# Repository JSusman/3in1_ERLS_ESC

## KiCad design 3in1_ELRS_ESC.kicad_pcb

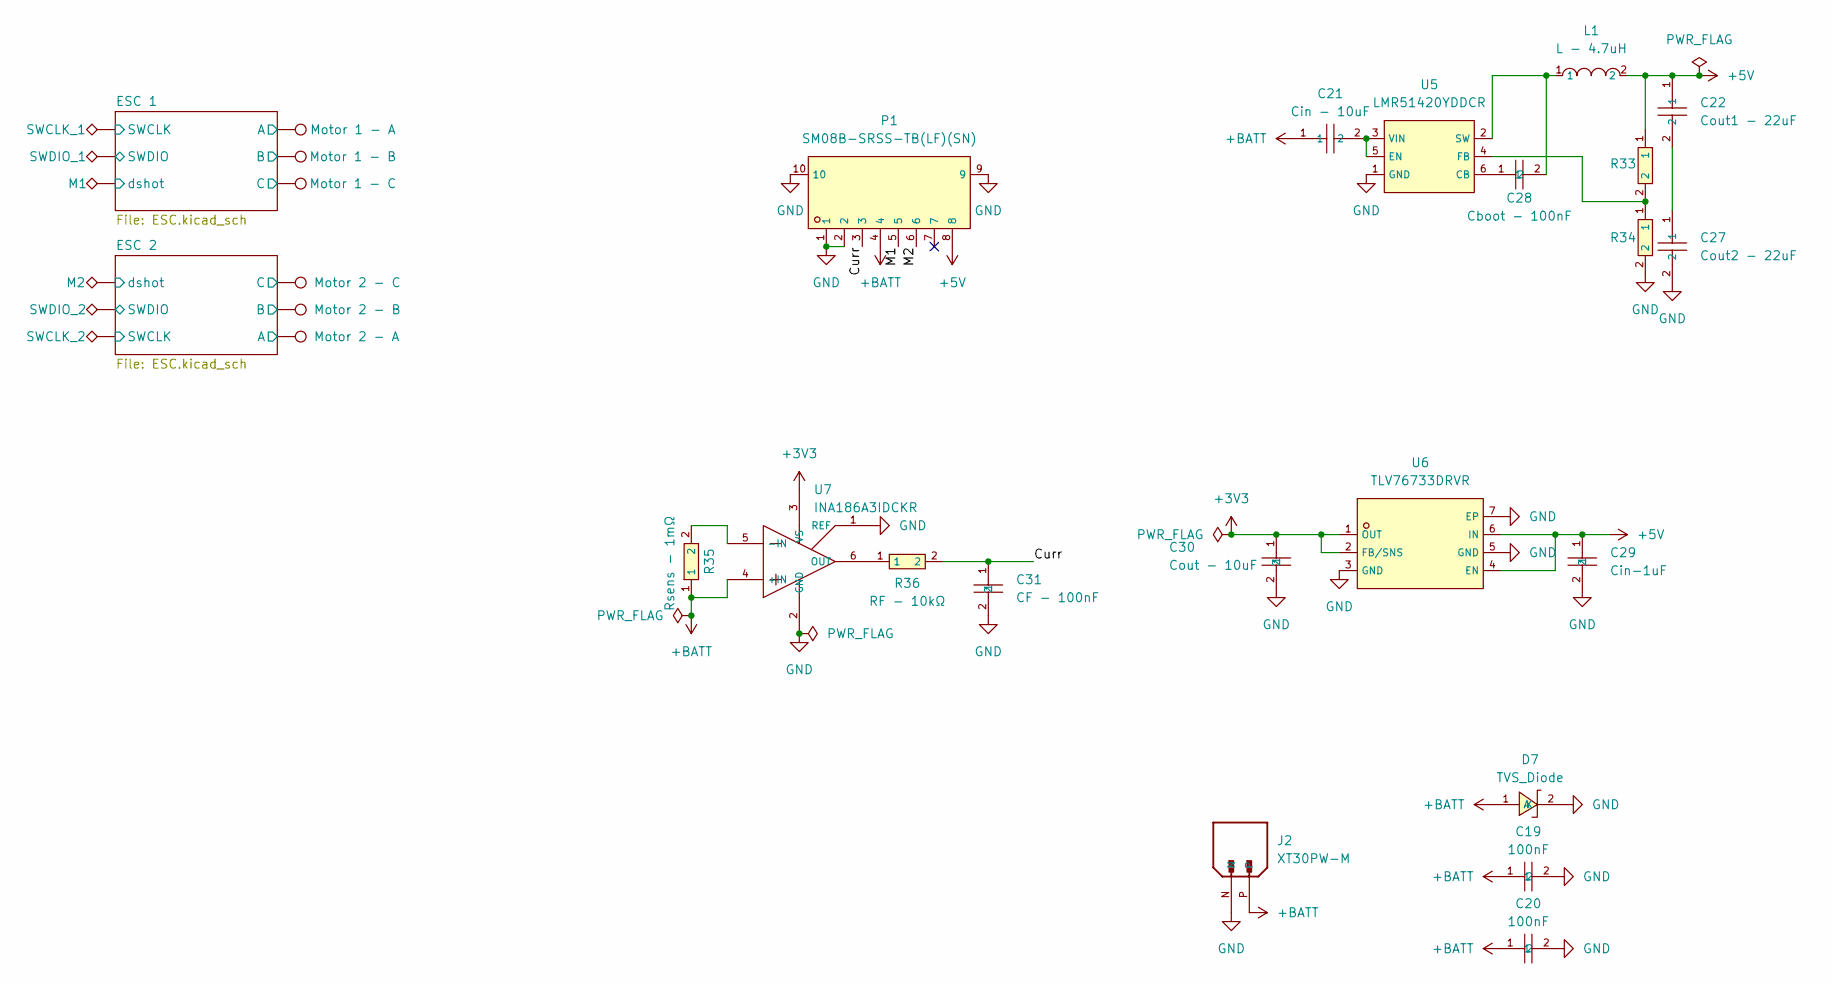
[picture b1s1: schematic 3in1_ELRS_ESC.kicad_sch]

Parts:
A1: Motor 1 - A; TestPoint_THTPad_2.5x2.5mm_Drill1.2mm
A2: Motor 2 - A; TestPoint_THTPad_2.5x2.5mm_Drill1.2mm
B1: Motor 1 - B; TestPoint_THTPad_2.5x2.5mm_Drill1.2mm
B2: Motor 2 - B; TestPoint_THTPad_2.5x2.5mm_Drill1.2mm
C1: Motor 1 - C; TestPoint_THTPad_2.5x2.5mm_Drill1.2mm
C2: Motor 2 - C; TestPoint_THTPad_2.5x2.5mm_Drill1.2mm
C19, C20: 100nF; C76937_C0201; LCSC C76937
C21: Cin - 10uF; C84416_C0805; LCSC C84416
C22: Cout1 - 22uF; C45783_C0805; LCSC C45783
C27: Cout2 - 22uF; C45783_C0805; LCSC C45783
C28: Cboot - 100nF; C76937_C0201; LCSC C76937
C29: Cin-1uF; C14445_C0402; LCSC C14445
C30: Cout - 10uF; C15525_C0402; LCSC C15525
C31: CF - 100nF; C76937_C0201; LCSC C76937
D7: TVS_Diode; C10213_SMB_L4_6-W3_6-LS5_3-RD; LCSC C10213
J2: XT30PW-M; AMASS_XT30PW-M; PARTREV 1.2
L1: L - 4.7uH; C2879693_IND-SMD_L4_5-W4_0; LCSC C2879693
M1, M2: TestPoint_THTPad_2.5x2.5mm_Drill1.2mm
P1: SM08B-SRSS-TB(LF)(SN); C160407_CONN-TH_SM08B-SRSS-TB-LF-SN; LCSC C160407
R33: Rtop - 100KΩ; C25530_R0402; LCSC C25530
R34: Rbot - 16.9KΩ; C11633_R0402; LCSC C11633
R35: Rsens - 1mΩ; C76287_R1206; LCSC C76287
R36: RF - 10kΩ; C149898_R0402; LCSC C149898
SWCLK_1, SWCLK_2: TestPoint_THTPad_2.5x2.5mm_Drill1.2mm
SWDIO_1, SWDIO_2: TestPoint_THTPad_2.5x2.5mm_Drill1.2mm
U5: LMR51420YDDCR; C5383002_SOT-23-6_L2_9-W1_6-P0_95-LS2_9-BL; LCSC C5383002
U6: TLV76733DRVR; C2848334_WSON-6_L2_0-W2_0-P0_65-TL-EP; LCSC C2848334
U7: INA186A3IDCKR; C2058245_SC-70-6_L2_0-W1_3-P0_65-LS2_1-BL-1; LCSC C2058245

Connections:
+3V3: C30.1, U6.1 (OUT), U6.2 (FB/SNS), U7.3 (VS); also elsewhere on the board
+5V: C22.1, C29.1, L1.2, P1.8, R33.1, U6.4 (EN), U6.6 (IN)
+BATT: C19.1, C20.1, C21.1, D7.1 (A), J2.P, P1.4, R35.1, U7.4 (+IN); also elsewhere on the board
/Curr: C31.1, P1.3, R36.2
/ESC 1/Motor A: A1.1 (1_1); also elsewhere on the board
/ESC 1/Motor B: B1.1 (1_1); also elsewhere on the board
/ESC 1/Motor C: C1.1 (1_1); also elsewhere on the board
/ESC 1/SWCLK: SWCLK_1.1 (1_1); also elsewhere on the board
/ESC 1/SWDIO: SWDIO_1.1 (1_1); also elsewhere on the board
/ESC 2/Motor A: A2.1 (1_1); also elsewhere on the board
/ESC 2/Motor B: B2.1 (1_1); also elsewhere on the board
/ESC 2/Motor C: C2.1 (1_1); also elsewhere on the board
/ESC 2/SWCLK: SWCLK_2.1 (1_1); also elsewhere on the board
/ESC 2/SWDIO: SWDIO_2.1 (1_1); also elsewhere on the board
/M1: P1.5
/M2: P1.6
GND: C19.2 (2_2), C20.2 (2_2), C27.2, C29.2, C30.2, C31.2, D7.2 (K), J2.N, P1.1, P1.2, P1.9, P1.10, R34.2, U5.1 (GND), U6.3 (GND), U6.5 (GND), U6.7 (EP), U7.1 (REF), U7.2 (GND); also elsewhere on the board
unnamed: C22.2, C27.1
unnamed: C28.1, U5.6 (CB)
unnamed: C21.2, U5.3 (VIN), U5.5 (EN)
unnamed: R33.2, R34.1, U5.4 (FB)
unnamed: C28.2, L1.1, U5.2 (SW)
unnamed: R35.2, U7.5 (-IN)
unnamed: R36.1, U7.6 (OUT)

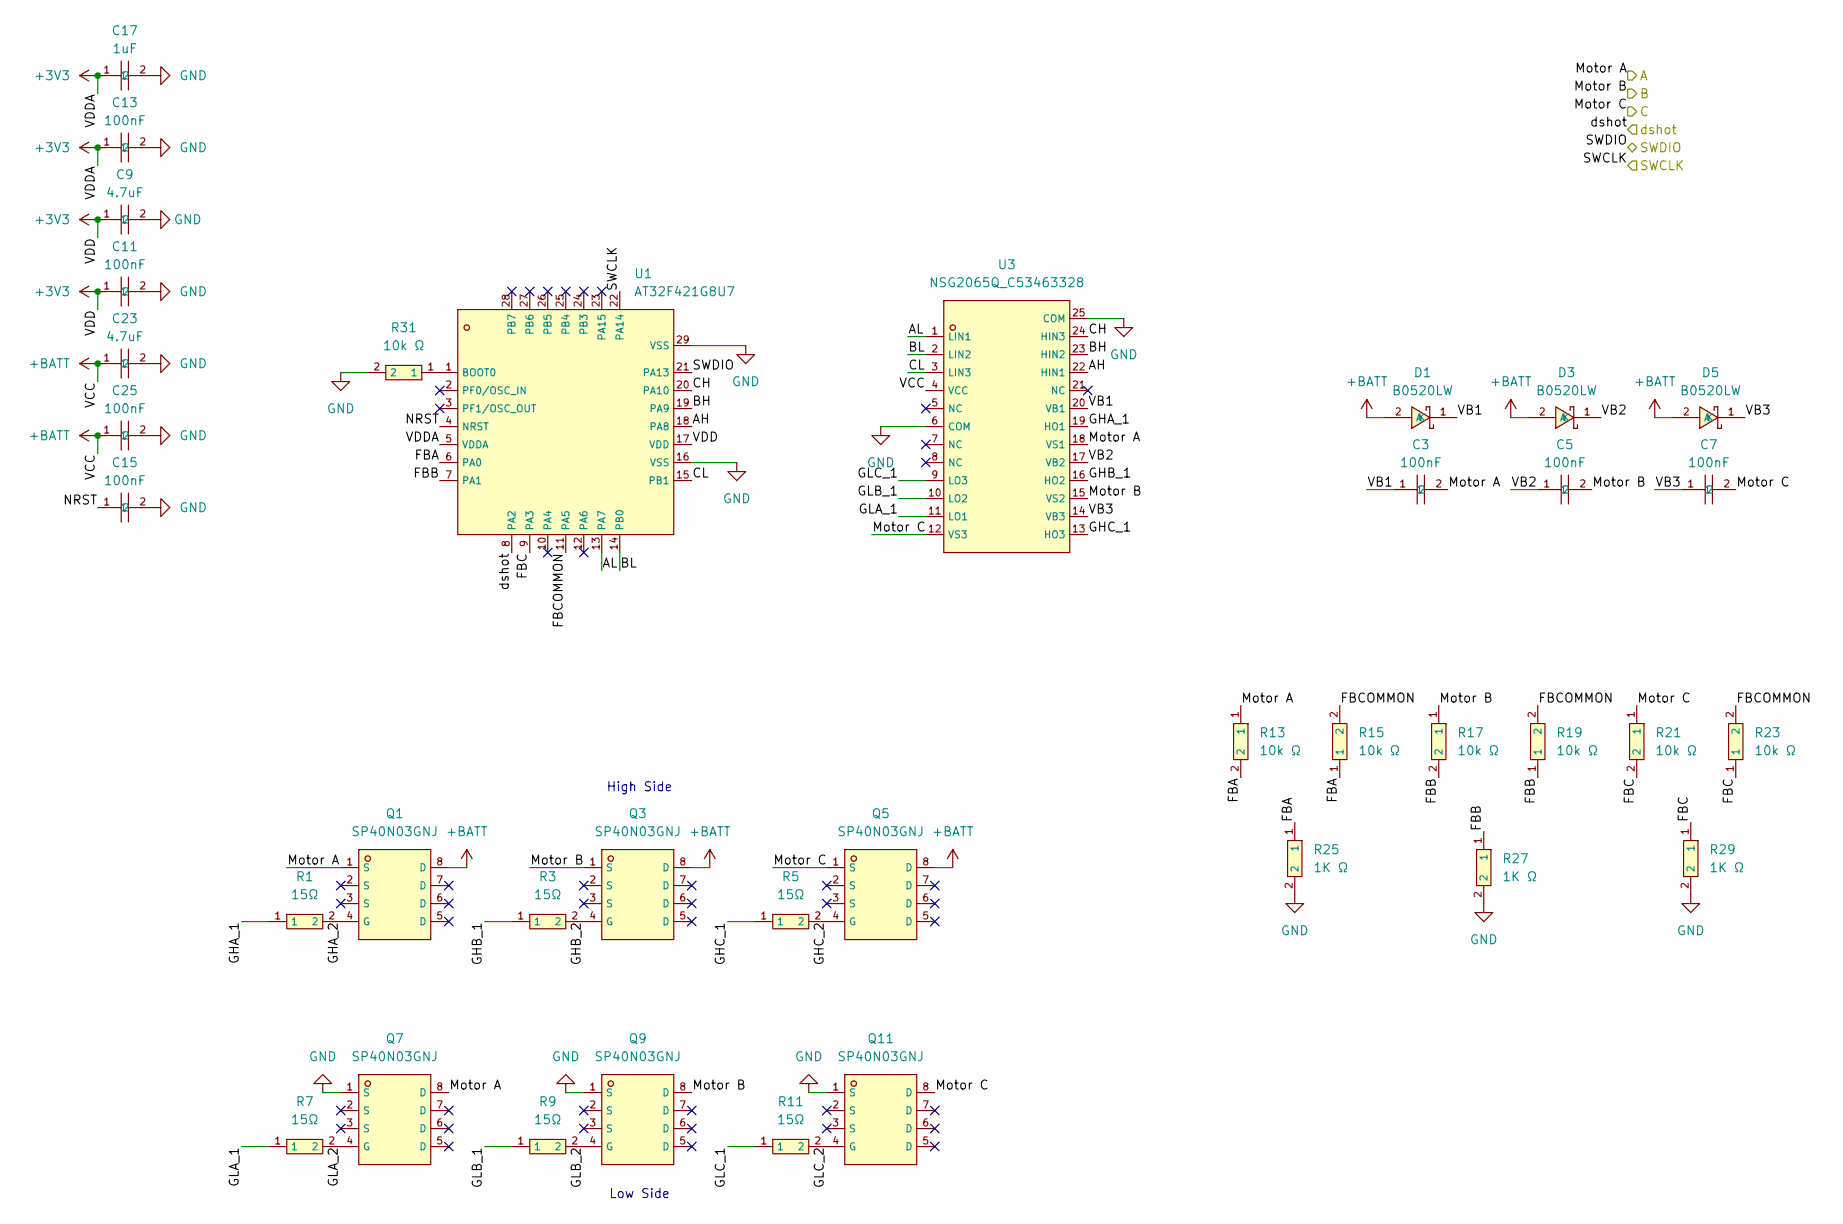
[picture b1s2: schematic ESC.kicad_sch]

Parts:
C3, C5, C7, C11, C13, C15, C25: 100nF; C76937_C0201; LCSC C76937
C9, C23: 4.7uF; C23687_C0402; LCSC C23687
C17: 1uF; C14445_C0402; LCSC C14445
D1, D3, D5: B0520LW; C89640_SOD-123_L2_8-W1_8-LS3_7-RD; LCSC C89640
Q1, Q3, Q5, Q7, Q9, Q11: SP40N03GNJ; C22466709_POWERPAK-1212-8_L3_0-W3_0-P0_65-LS3_3-BL; LCSC C22466709
R1, R3, R5, R7, R9, R11: 15Ω; C25083_R0402; LCSC C25083
R13, R15, R17, R19, R21, R23, R31: 10k Ω; C149898_R0402; LCSC C149898
R25, R27, R29: 1K Ω; C176101_R0402; LCSC C176101
U1: AT32F421G8U7; C2765098_QFN-28_L4_0-W4_0-P0_40-TL-EP2_4; LCSC C2765098
U3: NSG2065Q_C53463328; C53463328_QFN-24_L4_0-W4_0-P0_50-TL-EP2_8; LCSC C53463328

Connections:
+3V3: C9.1, C11.1, C13.1, C17.1, U1.5 (VDDA), U1.17 (VDD); also elsewhere on the board
+BATT: C23.1, C25.1, D1.2 (A), D3.2 (A), D5.2 (A), Q1.8 (D), Q3.8 (D), Q5.8 (D), U3.4 (VCC); also elsewhere on the board
/ESC 1/AH: U1.18 (PA8), U3.22 (HIN1)
/ESC 1/AL: U1.13 (PA7), U3.1 (LIN1)
/ESC 1/BH: U1.19 (PA9), U3.23 (HIN2)
/ESC 1/BL: U1.14 (PB0), U3.2 (LIN2)
/ESC 1/CH: U1.20 (PA10), U3.24 (HIN3)
/ESC 1/CL: U1.15 (PB1), U3.3 (LIN3)
/ESC 1/FBA: R13.2, R15.1, R25.1, U1.6 (PA0)
/ESC 1/FBB: R17.2, R19.1, R27.1, U1.7 (PA1)
/ESC 1/FBC: R21.2, R23.1, R29.1, U1.9 (PA3)
/ESC 1/FBCOMMON: R15.2, R19.2, R23.2, U1.11 (PA5)
/ESC 1/GHA_1: R1.1, U3.19 (HO1)
/ESC 1/GHA_2: Q1.4 (G), R1.2
/ESC 1/GHB_1: R3.1, U3.16 (HO2)
/ESC 1/GHB_2: Q3.4 (G), R3.2
/ESC 1/GHC_1: R5.1, U3.13 (HO3)
/ESC 1/GHC_2: Q5.4 (G), R5.2
/ESC 1/GLA_1: R7.1, U3.11 (LO1)
/ESC 1/GLA_2: Q7.4 (G), R7.2
/ESC 1/GLB_1: R9.1, U3.10 (LO2)
/ESC 1/GLB_2: Q9.4 (G), R9.2
/ESC 1/GLC_1: R11.1, U3.9 (LO3)
/ESC 1/GLC_2: Q11.4 (G), R11.2
/ESC 1/Motor A: C3.2, Q1.1 (S), Q7.8 (D), R13.1, U3.18 (VS1); also elsewhere on the board
/ESC 1/Motor B: C5.2, Q3.1 (S), Q9.8 (D), R17.1, U3.15 (VS2); also elsewhere on the board
/ESC 1/Motor C: C7.2, Q5.1 (S), Q11.8 (D), R21.1, U3.12 (VS3); also elsewhere on the board
/ESC 1/NRST: C15.1, U1.4 (NRST)
/ESC 1/SWCLK: U1.22 (PA14); also elsewhere on the board
/ESC 1/SWDIO: U1.21 (PA13); also elsewhere on the board
/ESC 1/VB1: C3.1, D1.1 (K), U3.20 (VB1)
/ESC 1/VB2: C5.1, D3.1 (K), U3.17 (VB2)
/ESC 1/VB3: C7.1, D5.1 (K), U3.14 (VB3)
/ESC 1/dshot: U1.8 (PA2)
GND: C9.2, C11.2, C13.2, C15.2, C17.2, C23.2 (2_2), C25.2 (2_2), Q7.1 (S), Q9.1 (S), Q11.1 (S), R25.2, R27.2, R29.2, R31.2, U1.16 (VSS), U1.29 (VSS), U3.6 (COM), U3.25 (COM); also elsewhere on the board
unnamed: R31.1, U1.1 (BOOT0)

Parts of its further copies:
C4, C6, C8, C12, C14, C16, C26: 100nF; C76937_C0201; LCSC C76937
C10, C24: 4.7uF; C23687_C0402; LCSC C23687
C18: 1uF; C14445_C0402; LCSC C14445
D2, D4, D6: B0520LW; C89640_SOD-123_L2_8-W1_8-LS3_7-RD; LCSC C89640
Q2, Q4, Q6, Q8, Q10, Q12: SP40N03GNJ; C22466709_POWERPAK-1212-8_L3_0-W3_0-P0_65-LS3_3-BL; LCSC C22466709
R2, R4, R6, R8, R10, R12: 15Ω; C25083_R0402; LCSC C25083
R14, R16, R18, R20, R22, R24, R32: 10k Ω; C149898_R0402; LCSC C149898
R26, R28, R30: 1K Ω; C176101_R0402; LCSC C176101
U2: AT32F421G8U7; C2765098_QFN-28_L4_0-W4_0-P0_40-TL-EP2_4; LCSC C2765098
U4: NSG2065Q_C53463328; C53463328_QFN-24_L4_0-W4_0-P0_50-TL-EP2_8; LCSC C53463328

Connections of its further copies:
+3V3: C10.1, C12.1, C14.1, C18.1, U2.5 (VDDA), U2.17 (VDD); also elsewhere on the board
+BATT: D2.2 (A), D4.2 (A), D6.2 (A); also elsewhere on the board
/ESC 2/AH: U2.18 (PA8), U4.22 (HIN1)
/ESC 2/AL: U2.13 (PA7), U4.1 (LIN1)
/ESC 2/BH: U2.19 (PA9), U4.23 (HIN2)
/ESC 2/BL: U2.14 (PB0), U4.2 (LIN2)
/ESC 2/CH: U2.20 (PA10), U4.24 (HIN3)
/ESC 2/CL: U2.15 (PB1), U4.3 (LIN3)
/ESC 2/FBA: R14.2, R16.1, R26.1, U2.6 (PA0)
/ESC 2/FBB: R18.2, R20.1, R28.1, U2.7 (PA1)
/ESC 2/FBC: R22.2, R24.1, R30.1, U2.9 (PA3)
/ESC 2/FBCOMMON: R16.2, R20.2, R24.2, U2.11 (PA5)
/ESC 2/GHA_1: R2.1, U4.19 (HO1)
/ESC 2/GHA_2: Q2.4 (G), R2.2
/ESC 2/GHB_1: R4.1, U4.16 (HO2)
/ESC 2/GHB_2: Q4.4 (G), R4.2
/ESC 2/GHC_1: R6.1, U4.13 (HO3)
/ESC 2/GHC_2: Q6.4 (G), R6.2
/ESC 2/GLA_1: R8.1, U4.11 (LO1)
/ESC 2/GLA_2: Q8.4 (G), R8.2
/ESC 2/GLB_1: R10.1, U4.10 (LO2)
/ESC 2/GLB_2: Q10.4 (G), R10.2
/ESC 2/GLC_1: R12.1, U4.9 (LO3)
/ESC 2/GLC_2: Q12.4 (G), R12.2
/ESC 2/Motor A: C4.2, Q2.1 (S), Q8.8 (D), R14.1, U4.18 (VS1); also elsewhere on the board
/ESC 2/Motor B: C6.2, Q4.1 (S), Q10.8 (D), R18.1, U4.15 (VS2); also elsewhere on the board
/ESC 2/Motor C: C8.2, Q6.1 (S), Q12.8 (D), R22.1, U4.12 (VS3); also elsewhere on the board
/ESC 2/NRST: C16.1, U2.4 (NRST)
/ESC 2/SWCLK: U2.22 (PA14); also elsewhere on the board
/ESC 2/SWDIO: U2.21 (PA13); also elsewhere on the board
/ESC 2/VB1: C4.1, D2.1 (K), U4.20 (VB1)
/ESC 2/VB2: C6.1, D4.1 (K), U4.17 (VB2)
/ESC 2/VB3: C8.1, D6.1 (K), U4.14 (VB3)
/ESC 2/dshot: U2.8 (PA2)
GND: C10.2, C12.2, C14.2, C16.2, C18.2, C24.2 (2_2), C26.2 (2_2), Q8.1 (S), Q10.1 (S), Q12.1 (S), R26.2, R28.2, R30.2, R32.2, U2.16 (VSS), U2.29 (VSS), U4.6 (COM), U4.25 (COM); also elsewhere on the board
unnamed: R32.1, U2.1 (BOOT0)

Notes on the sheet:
High Side
Low Side

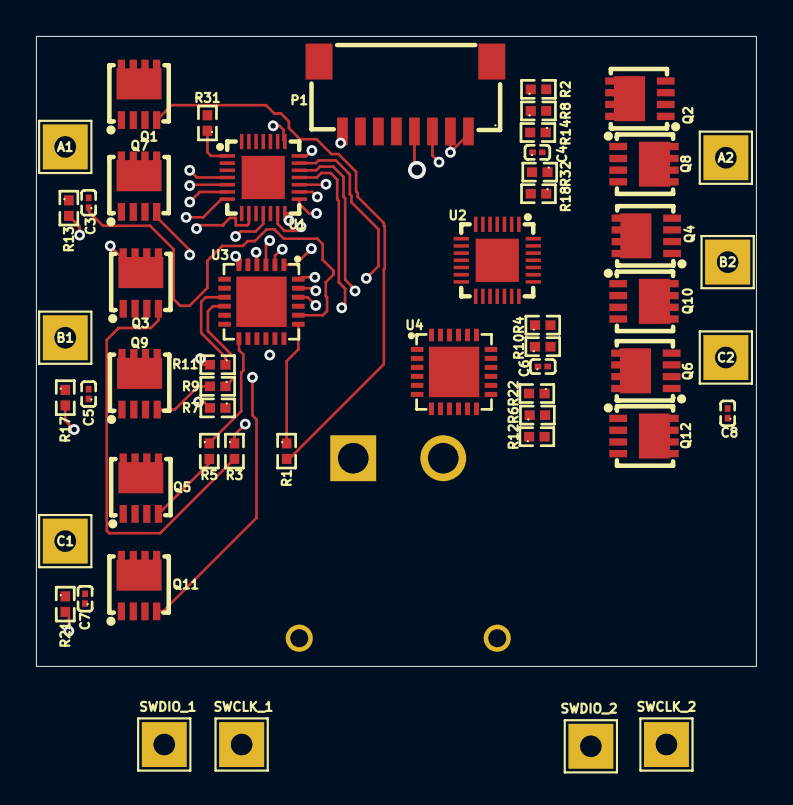
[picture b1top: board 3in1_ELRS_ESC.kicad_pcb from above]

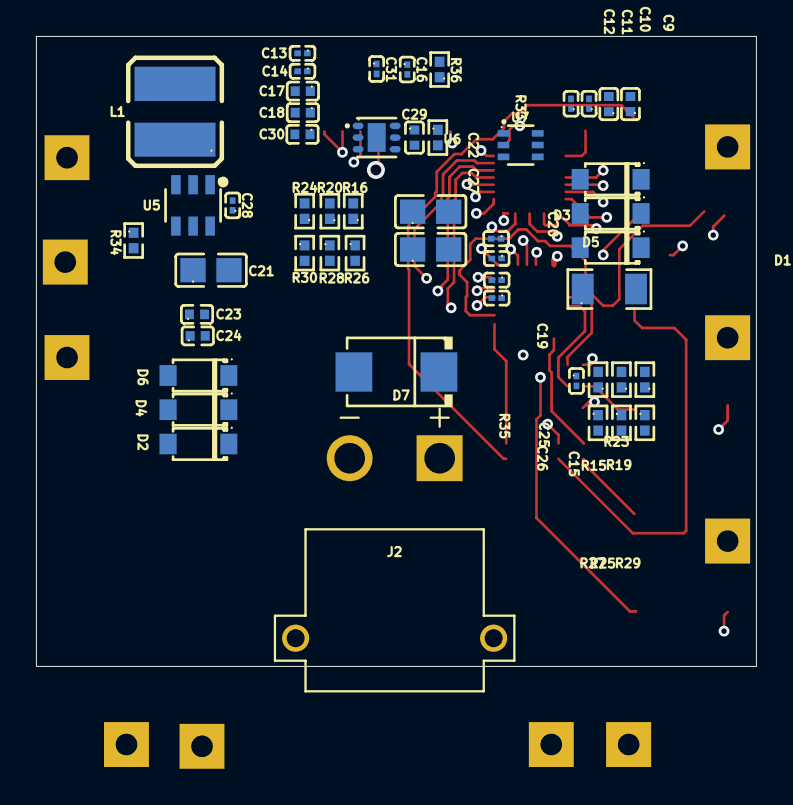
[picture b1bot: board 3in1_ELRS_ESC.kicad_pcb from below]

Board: 6 copper layers, 40.0 x 35.0 mm, 104 parts (51 on the bottom side), 76 nets.

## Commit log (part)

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2026-06-14 Schematic - Completed, PCB - Net Classes Assigned
2026-06-17 FET's Placed
2026-06-20 Bridges Placed
